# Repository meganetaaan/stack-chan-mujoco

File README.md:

# stack-chan-walk

**モノレポ移行:** シミュレーターは `software/sim/mujoco/`、CAD入力は `board/mechanical/design/` に移動しました。[配置・クリーン環境からの再現](docs/prototype/MONOREPO_ja.md)。下記の旧コマンドは `cd software/sim/mujoco` 後に実行してください。

# stack-chan MuJoCo RL

**高速旋回 r9:** MuJoCoで左右90°（停止誤差±1°以内）を6歩・約2.76秒で完了。名目条件と重量・摩擦の単独変動を含む10条件を検証済み。[再現手順・設計変更・結果](docs/FAST_TURN_RUN_ja.md)／[記録動画](validation/fast_turn_v1/left_turn.mp4)。既存r8とは別モデルです。

**WASDで操作（既定r9）:** `python teleop_yaw.py` — W/Sで前進・後退、A/Dで旋回。同時押しで曲線歩行、Shift＋WASDで向きを保った前後左右・斜めの並進。周期平均速度をフィードバック。キーを離すかSpaceで停止。[速度追従の仕様・評価](docs/VELOCITY_CONTROL_ja.md)。旧r8は `--profile r8`。[操作手順](docs/TELEOP_ja.md)

現在はTab5の顔と胴体・脚長・足形状を保ち、前進・後退・左右旋回・停止とその切替を検証しています。股関節ヨーを含む12軸のr8候補について、205秒・24区間の正式評価で固定20/20・ランダム化18/20の総合通過を確認しました。全40試行の状態記録からの再評価も一致しています。設計データ、制御・評価ソフト、全40試行の状態記録、成功・不合格の再生動画を公開しています。

[動作・切替の目標と基準](docs/MANEUVER_GOAL_ja.md)、[正式評価手順](docs/YAW_ACCEPTANCE_RUN_ja.md)、[凍結候補と正式評価記録](validation/yaw_acceptance_phase22_v1/README.md)、[開発20条件の結果と実状態動画](validation/yaw_backward_phase22_development_v1/README.md)を参照してください。実機検証は電源・パラメータ同定後、起き上がりは対象外です。

以下のR6の成績は従来の前進専用評価であり、新しい動作・切替の合格率には転用しません。

現行の胴体・脚長・足形状とTab5の顔を維持した、R6の残差強化学習を進めています。
現段階の受入条件は、0.10 m/s指令で10 m連続歩行を固定条件20/20、ランダム化条件18/20。
実機10 m・18/20は電源構成と実機同定後の次段階です。**固定具込みの仮定モデルで固定20/20、ランダム化18/20を達成**しました。電源・製作・実機の検証は未完了です。結果は `validation/r6_mounted_seed20260924`、方策は `policies/r6_mounted_seed20260924`、モデルは `assets/r6_mounted_battery`。ランダム化の関節制限逸脱1件・自己衝突1件も保存しています。

[学習と再現手順](docs/R6_RL_ja.md)、[受入条件](docs/GOAL_PROTOCOL_ja.md)、
[機構](docs/REAR_BRIDGE_ja.md)、[電源・電池](docs/POWER_ja.md)を参照してください。
初回の学習済み方策は `policies/r6_residual_seed20260920`、凍結モデルは `assets/r6_rear_bridge8_collision`。
以下は併存する旧R5-A環境の説明です。

MuJoCo と Stable-Baselines3（PPO）を使い、ｽﾀｯｸﾁｬﾝ R5-A の立位・歩行制御を検証するプロジェクトです。

現在の実装は v4 です。40 ms の目標角ローパスフィルターを制御経路へ組み込み、歩容と 0.02 m/s の速度追従を調整しています。詳しいセットアップ、学習・評価方法、既知の制限は [日本語ドキュメント](README_ja.md) を参照してください。

## 現在の状態

- 観測 61 次元、action 10 次元の PPO 方策
- v3 の学習済み actor から v4 制御条件への転送に対応
- オフライン回帰テスト 48 件と依存環境を使う runtime テストを収録
- v4 の歩行改善・収束は未実証

実行済み検査の範囲は [TEST_REPORT_ja.md](TEST_REPORT_ja.md)、変更点は [CHANGELOG_ja.md](CHANGELOG_ja.md) に記録しています。旧R5-A方策と作業用の `runs/`、`outputs/` はリポジトリに含めていません。R6方策は上記の公開ディレクトリへ整理しています。

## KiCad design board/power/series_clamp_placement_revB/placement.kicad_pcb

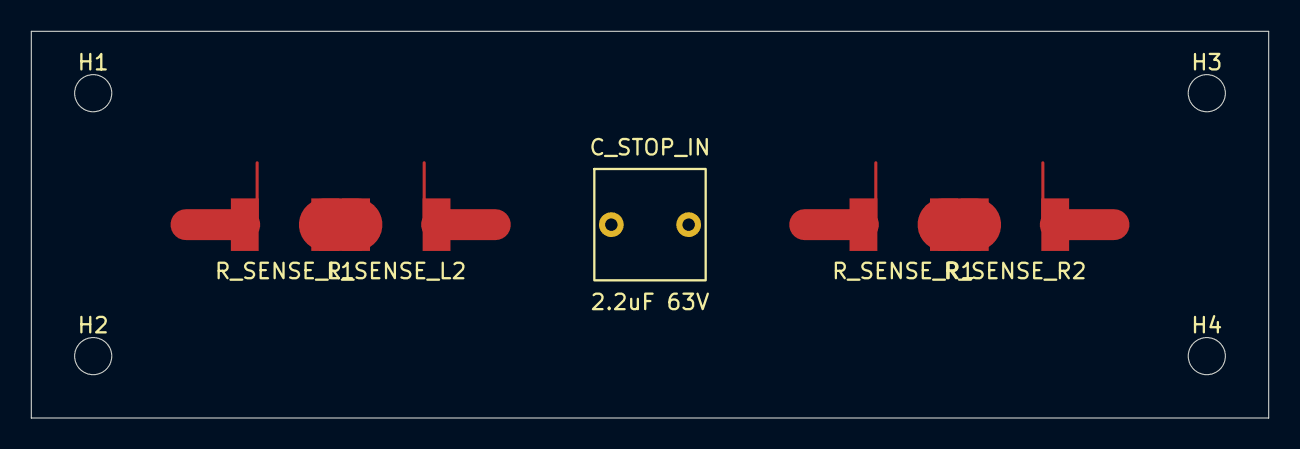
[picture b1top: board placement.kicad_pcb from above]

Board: 2 copper layers, 80.0 x 25.0 mm, 9 parts (0 on the bottom side), 2 nets.

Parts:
C_STOP_IN: 2.2uF 63V; WIMA_MKS2_7.2x7.2_P5_candidate
H1, H2, H3, H4: MountingHole_2.4mm_candidate
R_SENSE_L1, R_SENSE_L2: 4m; WSLF2512_candidate
R_SENSE_R1, R_SENSE_R2: 4m; WSLF2512_candidate

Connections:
L_SHUNT_MID: R_SENSE_L1.2, R_SENSE_L2.1
R_SHUNT_MID: R_SENSE_R1.2, R_SENSE_R2.1
